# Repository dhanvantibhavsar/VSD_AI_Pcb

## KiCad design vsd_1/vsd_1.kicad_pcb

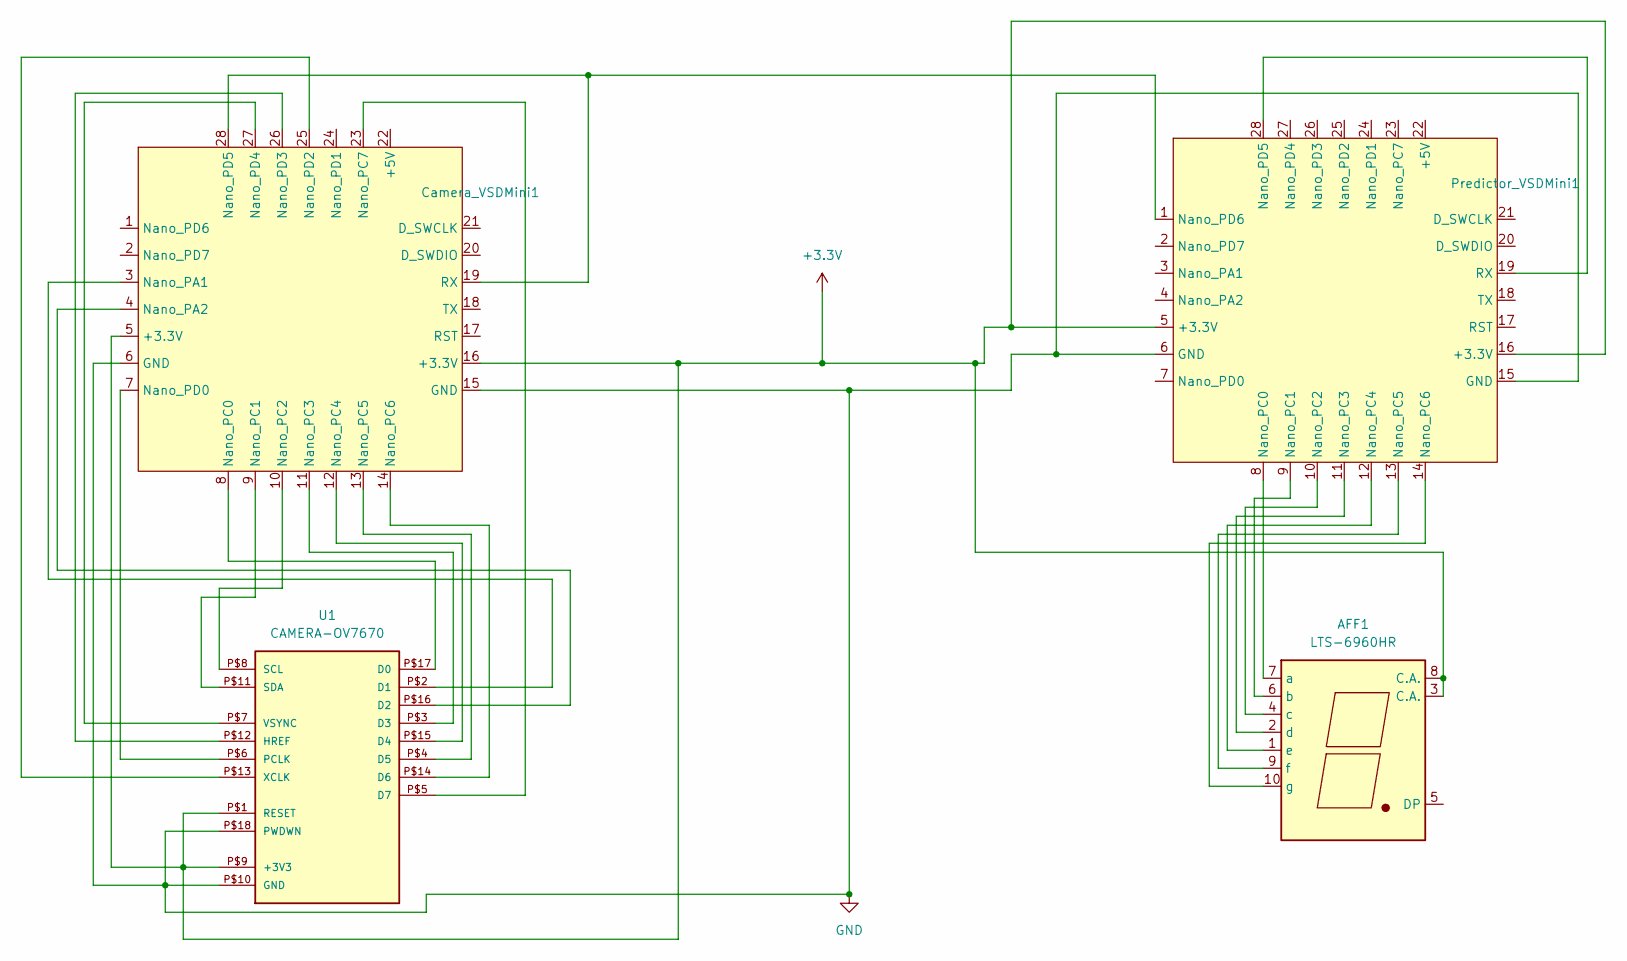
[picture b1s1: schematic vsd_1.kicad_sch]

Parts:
AFF1: LTS-6960HR; 7SegmentLED_LTS6760_LTS6780
Camera_VSDMini1: VSDSquadron Mini
Predictor_VSDMini1: VSDSquadron Mini
U1: CAMERA-OV7670; CAMERA-OV7670-DIP

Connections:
+3.3V: AFF1.3 (C.A.), AFF1.8 (C.A.), Camera_VSDMini1.5 (+3.3V), Camera_VSDMini1.16 (+3.3V), Predictor_VSDMini1.5 (+3.3V), Predictor_VSDMini1.16 (+3.3V), U1.P$1 (RESET), U1.P$9 (+3V3)
GND: Camera_VSDMini1.6 (GND), Camera_VSDMini1.15 (GND), Predictor_VSDMini1.6 (GND), Predictor_VSDMini1.15 (GND), U1.P$10 (GND), U1.P$18 (PWDWN)
unnamed: AFF1.7 (a), Predictor_VSDMini1.8 (Nano_PC0)
unnamed: AFF1.6 (b), Predictor_VSDMini1.9 (Nano_PC1)
unnamed: AFF1.4 (c), Predictor_VSDMini1.10 (Nano_PC2)
unnamed: AFF1.2 (d), Predictor_VSDMini1.11 (Nano_PC3)
unnamed: AFF1.1 (e), Predictor_VSDMini1.12 (Nano_PC4)
unnamed: AFF1.9 (f), Predictor_VSDMini1.13 (Nano_PC5)
unnamed: AFF1.10 (g), Predictor_VSDMini1.14 (Nano_PC6)
unnamed: Camera_VSDMini1.3 (Nano_PA1), U1.P$2 (D1)
unnamed: Camera_VSDMini1.4 (Nano_PA2), U1.P$16 (D2)
unnamed: Camera_VSDMini1.8 (Nano_PC0), U1.P$17 (D0)
unnamed: Camera_VSDMini1.9 (Nano_PC1), U1.P$11 (SDA)
unnamed: Camera_VSDMini1.10 (Nano_PC2), U1.P$8 (SCL)
unnamed: Camera_VSDMini1.11 (Nano_PC3), U1.P$3 (D3)
unnamed: Camera_VSDMini1.12 (Nano_PC4), U1.P$15 (D4)
unnamed: Camera_VSDMini1.13 (Nano_PC5), U1.P$4 (D5)
unnamed: Camera_VSDMini1.14 (Nano_PC6), U1.P$14 (D6)
unnamed: Camera_VSDMini1.23 (Nano_PC7), U1.P$5 (D7)
unnamed: Camera_VSDMini1.7 (Nano_PD0), U1.P$6 (PCLK)
unnamed: Camera_VSDMini1.25 (Nano_PD2), U1.P$13 (XCLK)
unnamed: Camera_VSDMini1.26 (Nano_PD3), U1.P$12 (HREF)
unnamed: Camera_VSDMini1.27 (Nano_PD4), U1.P$7 (VSYNC)
unnamed: Camera_VSDMini1.19 (RX), Camera_VSDMini1.28 (Nano_PD5), Predictor_VSDMini1.1 (Nano_PD6)
unnamed: Predictor_VSDMini1.19 (RX), Predictor_VSDMini1.28 (Nano_PD5)

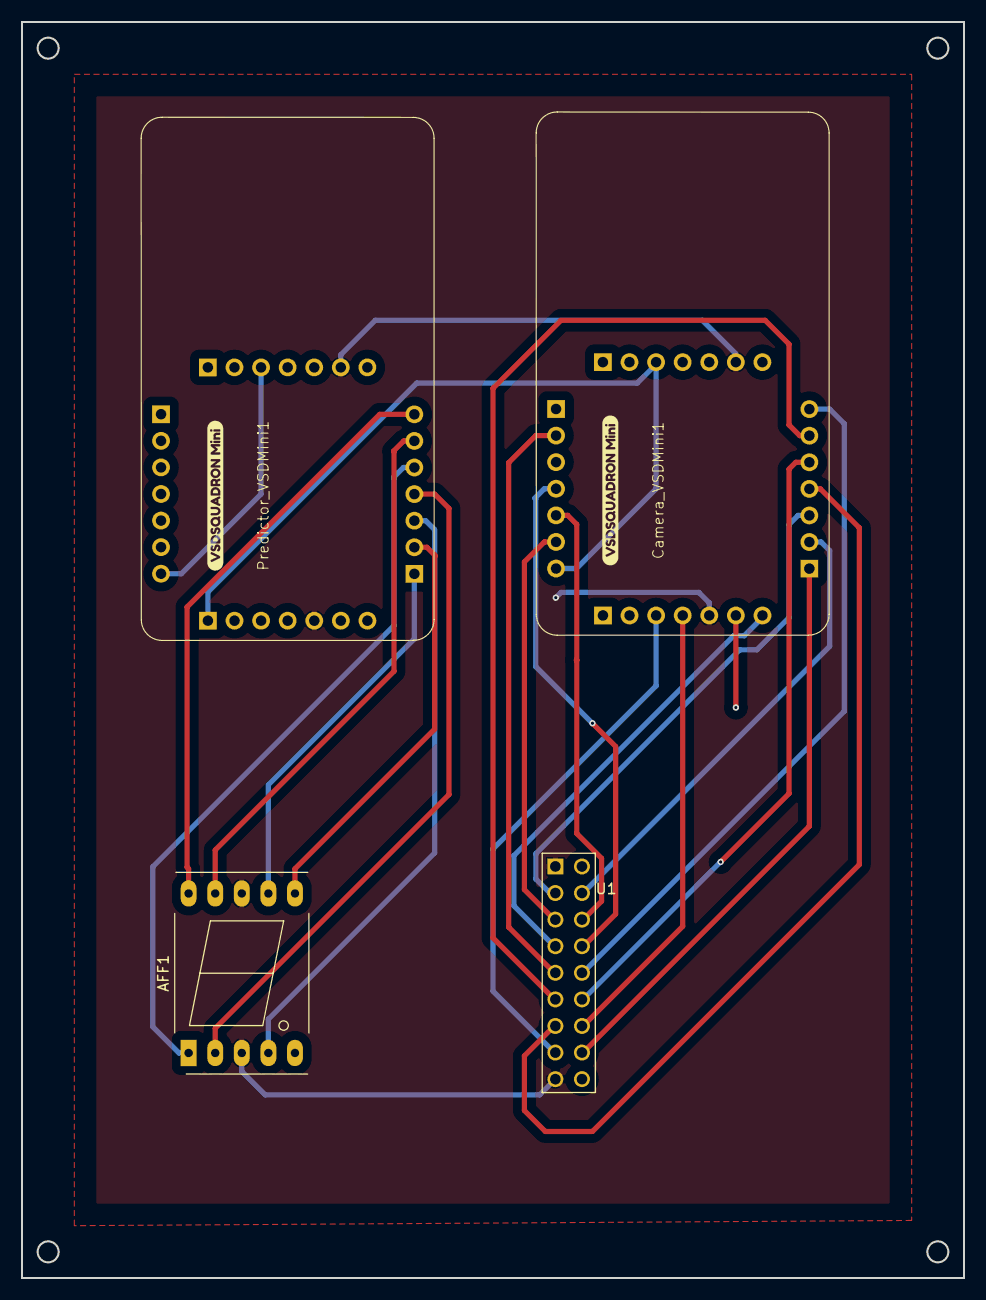
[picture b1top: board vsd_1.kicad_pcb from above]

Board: 2 copper layers, 90.0 x 120.0 mm, 4 parts (0 on the bottom side), 25 nets.

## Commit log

2024-08-23 initial commit with improved design for VSD AI
2024-08-23 added copper pour, and resolved issues introduced
